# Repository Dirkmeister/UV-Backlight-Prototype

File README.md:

# UV-Backlight-Prototype
 A UV led backlight for pcb imaging. PCB is designed for prototyping.

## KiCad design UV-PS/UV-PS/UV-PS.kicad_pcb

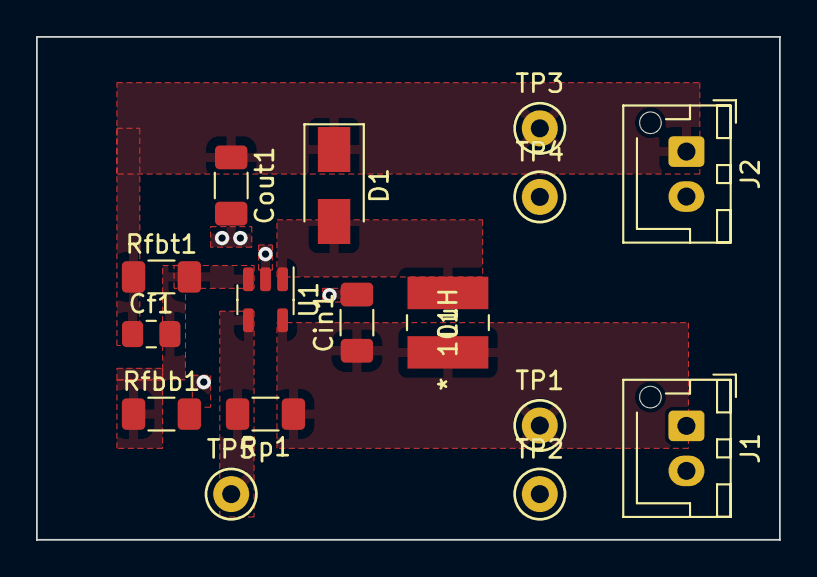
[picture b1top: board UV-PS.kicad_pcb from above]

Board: 2 copper layers, 41.3 x 27.9 mm, 16 parts (0 on the bottom side), 6 nets, no tracks yet.

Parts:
Cf1: 390pF; C_0805_2012Metric_Pad1.18x1.45mm_HandSolder
Cin1: 4.7uF; C_1206_3216Metric_Pad1.33x1.80mm_HandSolder
Cout1: 4.7uF; C_1206_3216Metric_Pad1.33x1.80mm_HandSolder
D1: 410mV 1A; D_SMA
J1, J2: Conn_01x02_Female; JST_XH_B2B-XH-AM_1x02_P2.50mm_Vertical
L1: 10uH; SDR0403-100ML
Rfbb1: 14.3kΩ; R_1206_3216Metric_Pad1.30x1.75mm_HandSolder
Rfbt1: 267kΩ; R_1206_3216Metric_Pad1.30x1.75mm_HandSolder
Rp1: 1MΩ; R_1206_3216Metric_Pad1.30x1.75mm_HandSolder
TP1: Vin,1; TestPoint_Keystone_5000-5004_Miniature
TP2, TP4: Gnd; TestPoint_Keystone_5000-5004_Miniature
TP3: Vout,1; TestPoint_Keystone_5000-5004_Miniature
TP5: En; TestPoint_Keystone_5000-5004_Miniature
U1: LMR64010XMF; SOT-23-5

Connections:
/Vin,1: Cin1.1, L1.1, Rp1.1, TP1.1, U1.5 (VIN)
/Vout,1: Cf1.1, Cout1.1, D1.1 (K), J2.1, Rfbt1.1, TP3.1
GND: Cin1.2, Cout1.2, J1.2, J2.2, Rfbb1.2, TP2.1, TP4.1, U1.2 (GND)
unnamed: Cf1.2, Rfbb1.1, Rfbt1.2, U1.3 (FB)
unnamed: D1.2 (A), L1.2, U1.1 (SW)
unnamed: Rp1.2, TP5.1, U1.4 (EN)

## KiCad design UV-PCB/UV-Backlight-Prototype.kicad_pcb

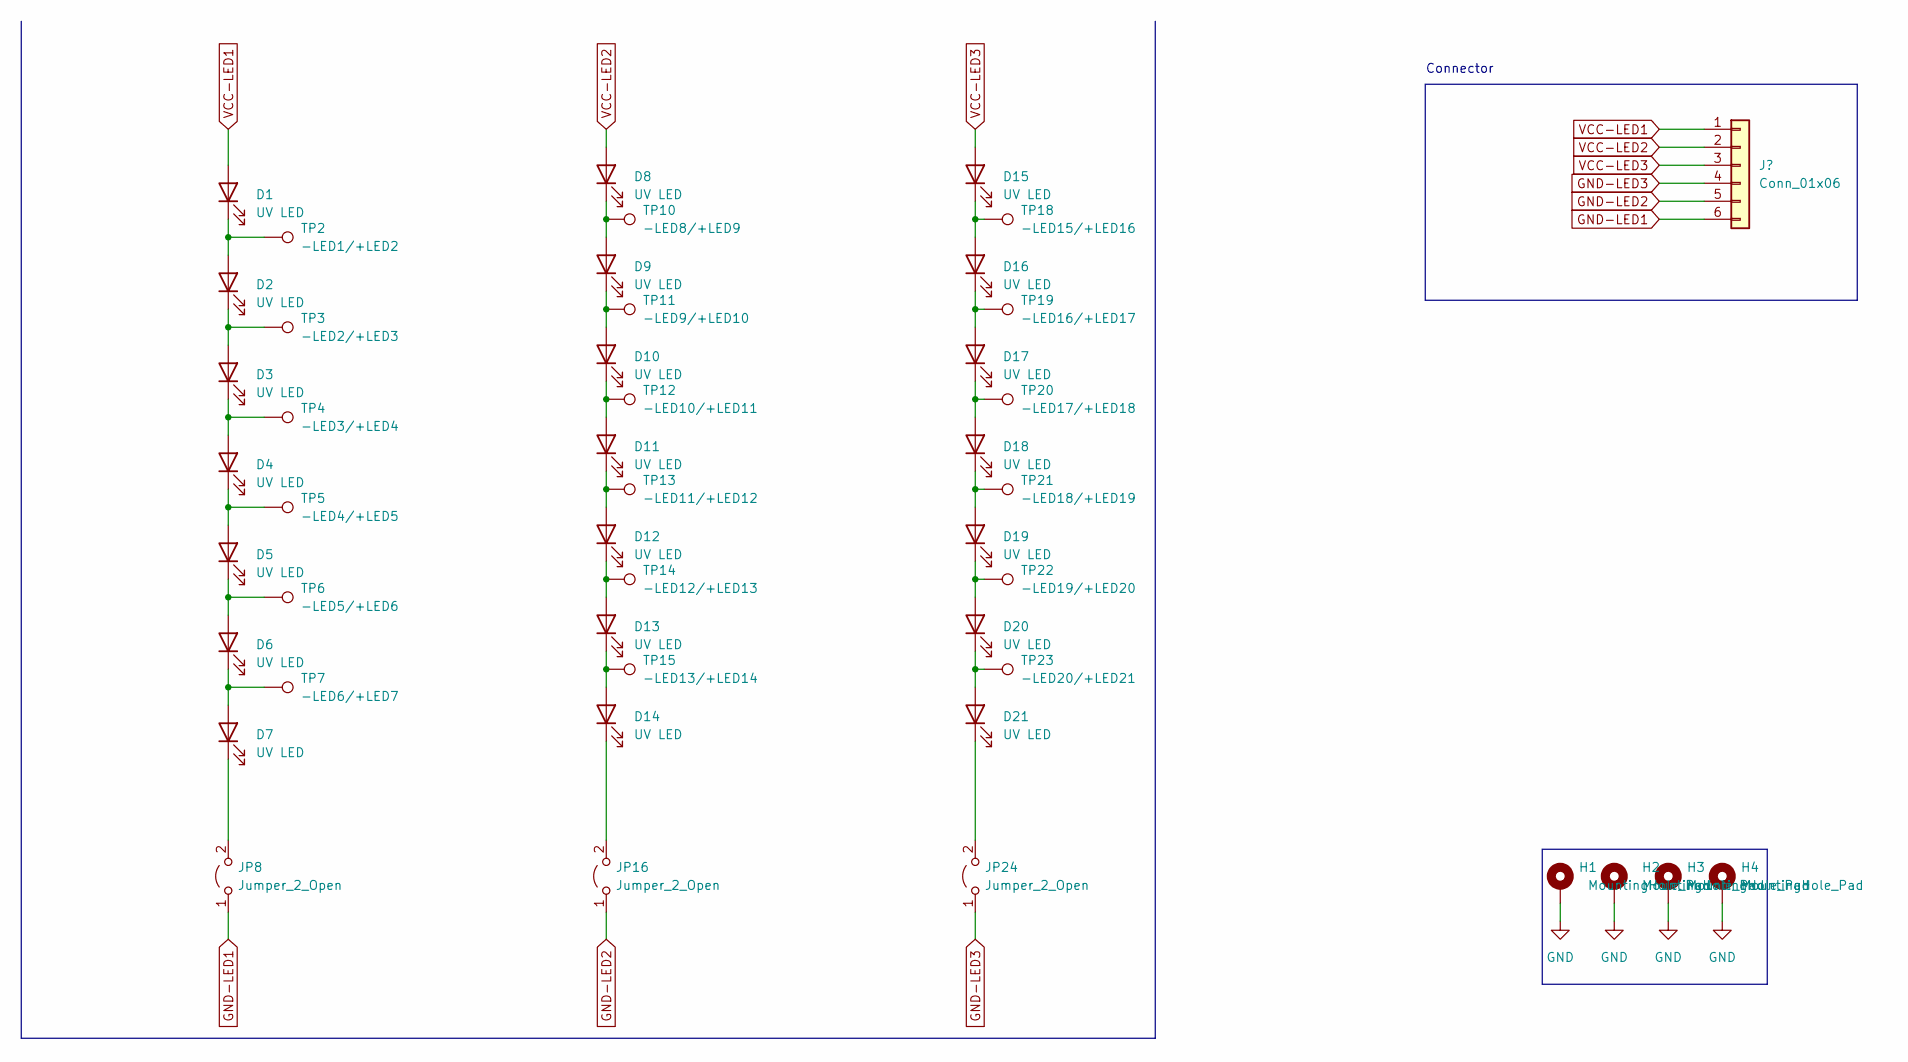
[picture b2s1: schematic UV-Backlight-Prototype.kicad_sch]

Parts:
D1, D2, D3, D4, D5, D6, D7, D8, D9, D10, D11, D12, D13, D14, D15, D16, D17, D18, D19, D20, D21: UV LED; LED_PLCC_2835_Handsoldering
H1, H2, H3, H4: MountingHole_Pad; MountingHole_3.2mm_M3_Pad_Via
JP8, JP16, JP24: Jumper_2_Open; PinHeader_1x02_P2.54mm_Vertical
TP2: -LED1/+LED2; TestPoint_Keystone_5000-5004_Miniature
TP3: -LED2/+LED3; TestPoint_Keystone_5000-5004_Miniature
TP4: -LED3/+LED4; TestPoint_Keystone_5000-5004_Miniature
TP5: -LED4/+LED5; TestPoint_Keystone_5000-5004_Miniature
TP6: -LED5/+LED6; TestPoint_Keystone_5000-5004_Miniature
TP7: -LED6/+LED7; TestPoint_Keystone_5000-5004_Miniature
TP10: -LED8/+LED9; TestPoint_Keystone_5000-5004_Miniature
TP11: -LED9/+LED10; TestPoint_Keystone_5000-5004_Miniature
TP12: -LED10/+LED11; TestPoint_Keystone_5000-5004_Miniature
TP13: -LED11/+LED12; TestPoint_Keystone_5000-5004_Miniature
TP14: -LED12/+LED13; TestPoint_Keystone_5000-5004_Miniature
TP15: -LED13/+LED14; TestPoint_Keystone_5000-5004_Miniature
TP18: -LED15/+LED16; TestPoint_Keystone_5000-5004_Miniature
TP19: -LED16/+LED17; TestPoint_Keystone_5000-5004_Miniature
TP20: -LED17/+LED18; TestPoint_Keystone_5000-5004_Miniature
TP21: -LED18/+LED19; TestPoint_Keystone_5000-5004_Miniature
TP22: -LED19/+LED20; TestPoint_Keystone_5000-5004_Miniature
TP23: -LED20/+LED21; TestPoint_Keystone_5000-5004_Miniature

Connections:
GND: H1.1, H2.1, H3.1, H4.1
GND-LED1: JP8.1 (A); also elsewhere on the board
GND-LED2: JP16.1 (A); also elsewhere on the board
GND-LED3: JP24.1 (A); also elsewhere on the board
unnamed: D1.1 (K), D2.2 (A), TP2.1
unnamed: D2.1 (K), D3.2 (A), TP3.1
unnamed: D3.1 (K), D4.2 (A), TP4.1
unnamed: D4.1 (K), D5.2 (A), TP5.1
unnamed: D5.1 (K), D6.2 (A), TP6.1
unnamed: D6.1 (K), D7.2 (A), TP7.1
unnamed: D7.1 (K), JP8.2 (B)
unnamed: D8.1 (K), D9.2 (A), TP10.1
unnamed: D10.1 (K), D11.2 (A), TP12.1
unnamed: D9.1 (K), D10.2 (A), TP11.1
unnamed: D11.1 (K), D12.2 (A), TP13.1
unnamed: D12.1 (K), D13.2 (A), TP14.1
unnamed: D13.1 (K), D14.2 (A), TP15.1
unnamed: D14.1 (K), JP16.2 (B)
unnamed: D15.1 (K), D16.2 (A), TP18.1
unnamed: D16.1 (K), D17.2 (A), TP19.1
unnamed: D17.1 (K), D18.2 (A), TP20.1
unnamed: D18.1 (K), D19.2 (A), TP21.1
unnamed: D19.1 (K), D20.2 (A), TP22.1
unnamed: D20.1 (K), D21.2 (A), TP23.1
unnamed: D21.1 (K), JP24.2 (B)
VCC-LED1: D1.2 (A); also elsewhere on the board
VCC-LED2: D8.2 (A); also elsewhere on the board
VCC-LED3: D15.2 (A); also elsewhere on the board

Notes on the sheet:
Connector

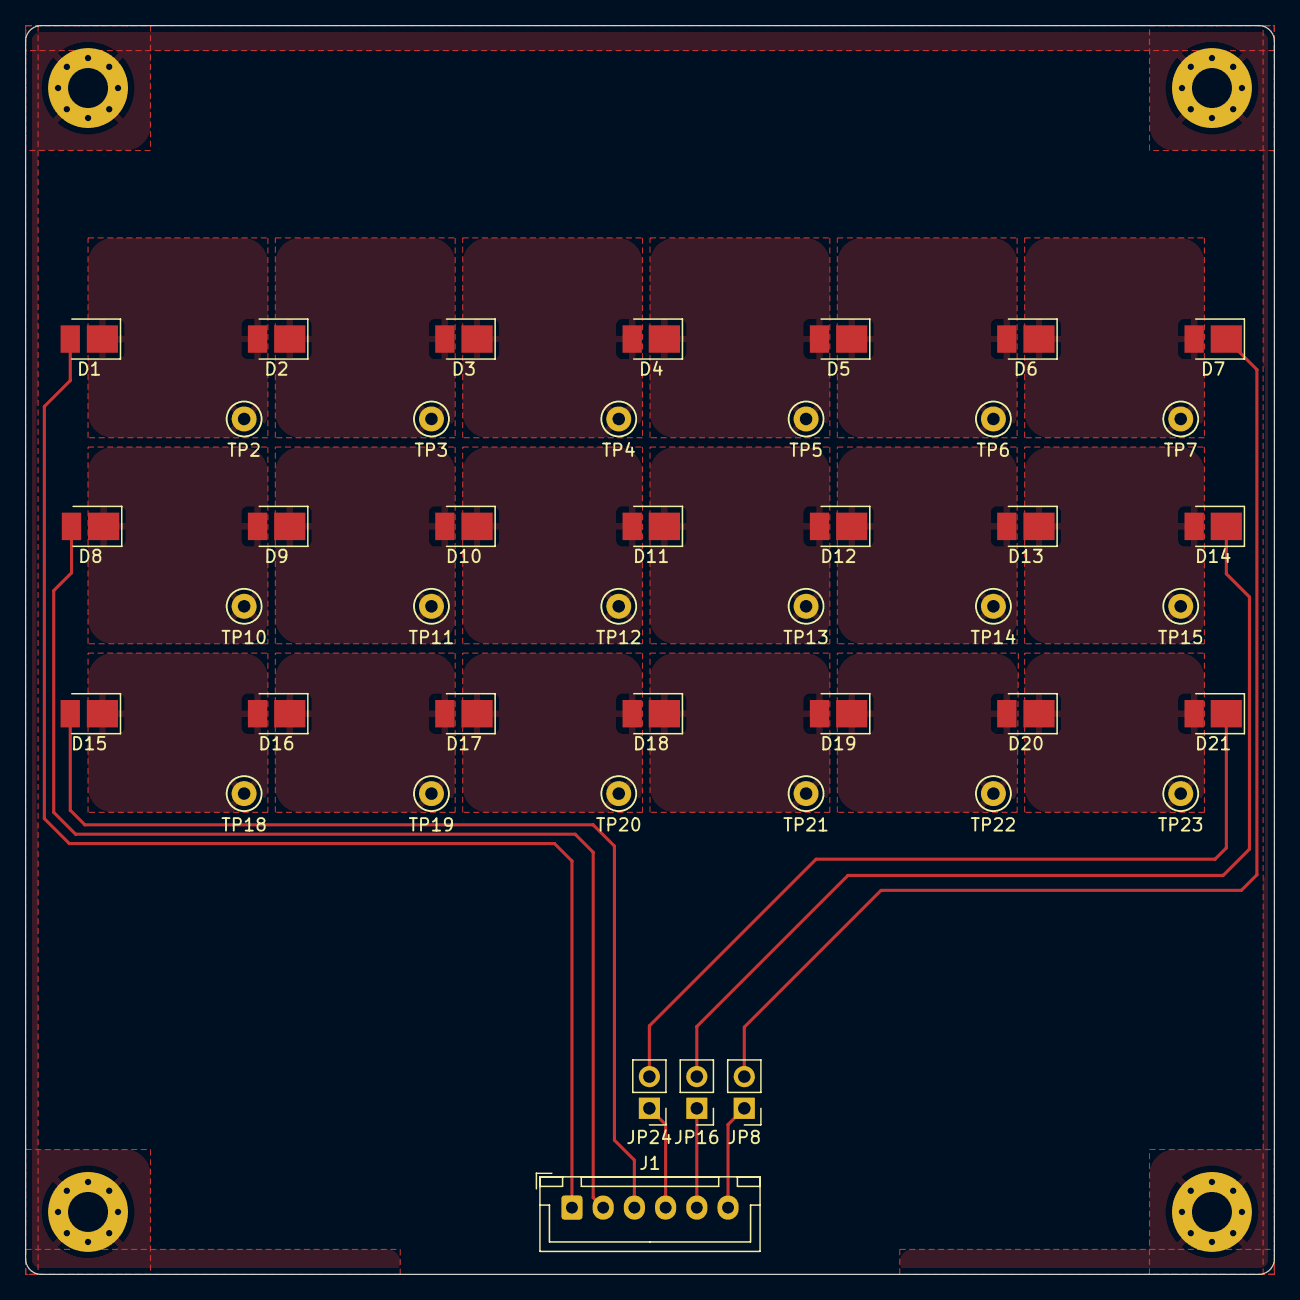
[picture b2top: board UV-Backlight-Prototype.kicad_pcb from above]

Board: 2 copper layers, 100.0 x 100.0 mm, 47 parts (0 on the bottom side), 28 nets.

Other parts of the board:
J1: Conn_01x06; JST_XH_B6B-XH-A_1x06_P2.50mm_Vertical

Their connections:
GND-LED1: J1.6; also elsewhere on the board
GND-LED2: J1.5; also elsewhere on the board
GND-LED3: J1.4; also elsewhere on the board
VCC-LED1: J1.1; also elsewhere on the board
VCC-LED2: J1.2; also elsewhere on the board
VCC-LED3: J1.3; also elsewhere on the board

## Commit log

2022-10-24 Initialize Project
2022-10-26 Schematic Update
    Added Schematic LED arrays and thermsistors
2022-10-30 Connector
    Connector Schematic update
2022-11-05 Update UV-Backlight-Prototype.kicad_sch
    Added Test points to each LED NET
    Added 0 ohm jumper for matrix config
2022-11-05 Schematic
    Assigned footprints
2022-11-05 Update UV-Backlight-Prototype.kicad_sch
    Added Mounting holes to schematic. M3 mounting holes, connected to ground, vias around hole for aesthetics
2022-11-05 Update UV-Backlight-Prototype.kicad_pcb
    PCB Creation
2022-11-05 Update UV-Backlight-Prototype.kicad_pcb
    outline, mounting hole, connectors
2022-11-05 Autosave
    autosave
2022-11-06 LED Placement
    Drawings of the LEDs , with the outline and mounting holes
2022-11-06 Outline
    Save
2022-11-06 LED-Outline
    Reference drawing update. DXF creation
2022-11-06 LED-OUTLINE
    AUTOSAVE
2022-11-06 Update LED_LAYOUT_TO-KiCAD.dwg
    Did not import to kicad correctly. Changed all objects to same layer and same linetype
2022-11-06 PCB
    Import LED outline DXF into PCB-New
2022-12-05 Progress Update
    Changes to PCB:
    Adjusted LED placement
    Started Test point placement
    Changes to schematic:
    Test points for VCC and GND for LED strings 1,2,3 deemed redundant and removed.
2022-12-05 PCB
    Component placement complete
    Added a section for testpoints for only the thermistors.
    Open space bottom right - Add perfboard for prototyping CC drivers
2022-12-17 Sent to production
    PCB created and sent to production for the first prototype
2023-01-07 Restructured folder setups
    Starting prototypes for the power supply and constant current source
2023-01-07 UV Backlight and PS
    Power Supply creation
    V2 for backlight, removed thermsistors
    Changed the connector, simplified the board
2023-01-14 Power Supply Schematic Complete
2023-02-01 IC Change
    Changed complete design.
    From Mc33062 to LMR64010

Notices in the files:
parts and their libraries:
Copyright 2021 Accelerated Designs. All rights reserved.
